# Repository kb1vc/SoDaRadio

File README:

SoDa -- A Software Defined Radio for the Ettus Research USRP

SoDaRadio is a multi-mode VHF/UHF/Microwave radio transciever
that runs on Linux.   It has been tested on several Ettus
USRP models including the N200/WBX, N210/WBX, N210/SBX, N200/UBX,
and the B210. 

For information on building, installing, and using SoDaRadio see
the github pages at https://kb1vc.github.io/SoDaRadio/

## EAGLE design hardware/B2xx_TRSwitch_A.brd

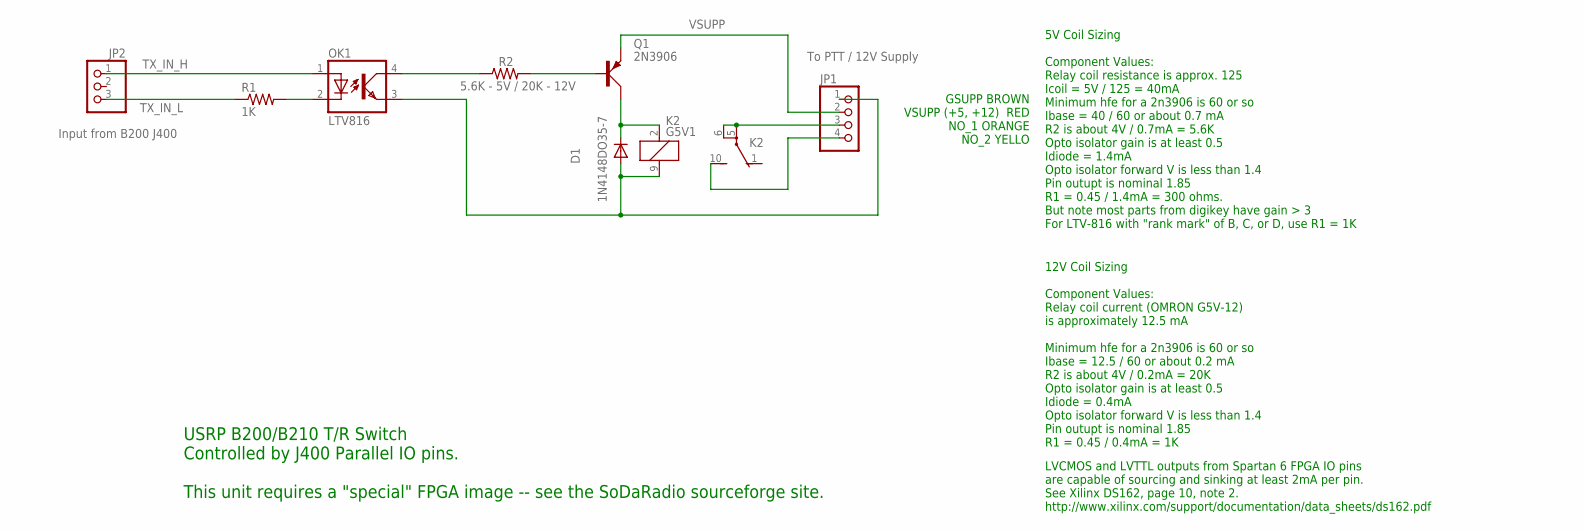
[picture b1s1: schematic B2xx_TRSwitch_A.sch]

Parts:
D1: 1N4148DO35-7; DO35-7
JP1: To PTT / 12V Supply; 1X04
JP2: Input from B200 J400; 1X03
K2: G5V1
OK1: LTV816; DIL04
Q1: 2N3906; TO92D
R1: 1K; AXIAL-0.3
R2: 5.6K - 5V / 20K - 12V; AXIAL-0.3

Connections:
GSUP_GND: D1.A, JP1.1, K2.9 (2), OK1.3 (EMIT)
unnamed: OK1.2 (C), R1.P$2 (2)
unnamed: OK1.4 (COL), R2.P$1 (1)
unnamed: Q1.B, R2.P$2 (2)
unnamed: D1.C, K2.2 (1), Q1.C
unnamed: JP1.3, K2.5, K2.6
unnamed: JP1.4, K2.10 (S)
TX_IN_H: JP2.1, OK1.1 (A)
TX_IN_L: JP2.3, R1.P$1 (1)
VSUPP: JP1.2, Q1.E

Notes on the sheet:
5V Coil Sizing Component Values: Relay coil resistance is approx. 125 Icoil = 5V / 125 = 40mA Minimum hfe for a 2n3906 is 60 or so Ibase = 40 / 60 or about 0.7 mA R2 is about 4V / 0.7mA = 5.6K Opto isolator gain is at least 0.5 Idiode = 1.4mA Opto isolator forward V is less than 1.4 Pin outupt is n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
12V Coil Sizing Component Values: Relay coil current (OMRON G5V-12) is approximately 12.5 mA Minimum hfe for a 2n3906 is 60 or so Ibase = 12.5 / 60 or about 0.2 mA R2 is about 4V / 0.2mA = 20K Opto isolator gain is at least 0.5 Idiode = 0.4mA Opto isolator forward V is less than 1.4 Pin outupt is n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
GSUPP BROWN VSUPP (+5, +12) RED NO_1 ORANGE NO_2 YELLO
LVCMOS and LVTTL outputs from Spartan 6 FPGA IO pins are capable of sourcing and sinking at least 2mA per pin. See Xilinx DS162, page 10, note 2. http://www.xilinx.com/support/documentation/data_sheets/ds162.pdf
USRP B200/B210 T/R Switch Controlled by J400 Parallel IO pins. This unit requires a "special" FPGA image -- see the SoDaRadio sourceforge site.

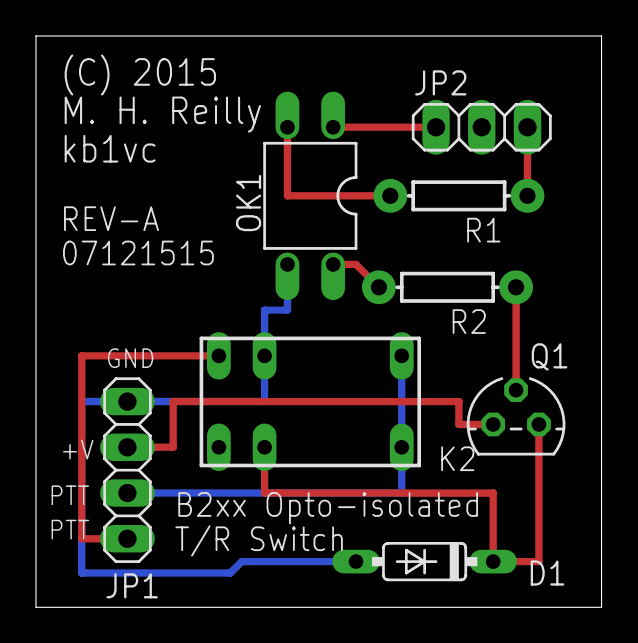
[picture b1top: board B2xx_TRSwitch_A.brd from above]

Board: 2 copper layers, 31.4 x 31.7 mm, 8 parts (0 on the bottom side), 10 nets.

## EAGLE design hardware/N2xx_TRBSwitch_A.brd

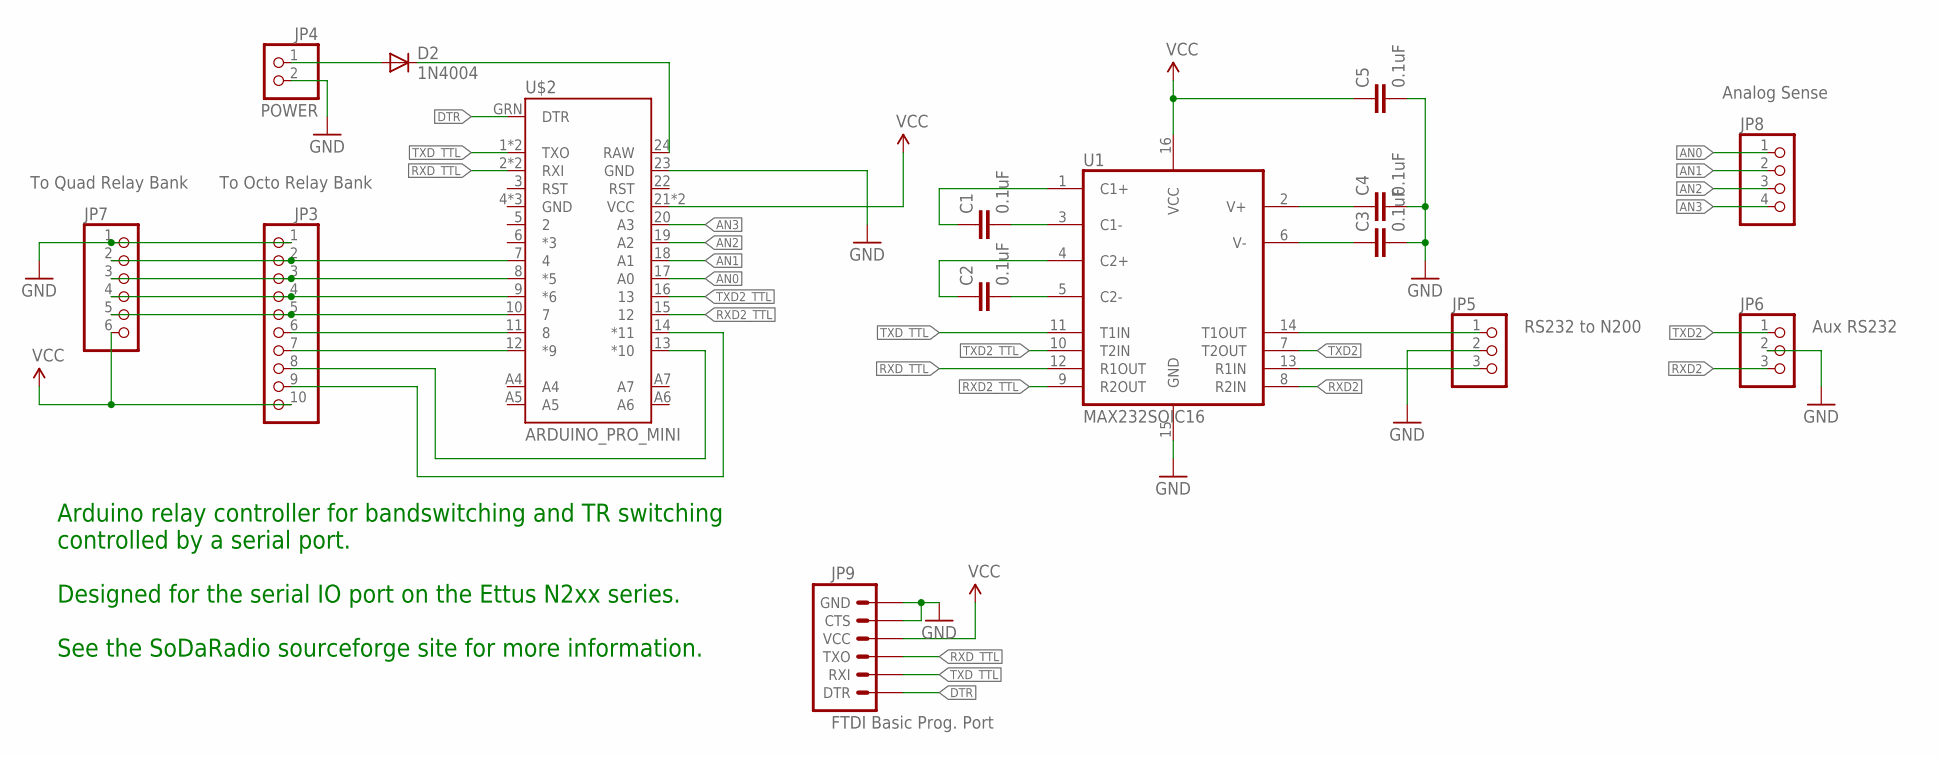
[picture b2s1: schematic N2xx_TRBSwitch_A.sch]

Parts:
C1, C2, C3, C4, C5: 0.1uF; 0805
D2: 1N4004; DO41-10
JP3: To Octo Relay Bank; 1X10
JP4: POWER; 1X02
JP5: RS232 to N200; 1X03
JP6: Aux RS232; 1X03
JP7: To Quad Relay Bank; 1X06
JP8: Analog Sense; 1X04
JP9: FTDI Basic Prog. Port; 1X06
U1: MAX232SOIC16; SO016
U$2: ARDUINO_PRO_MINI

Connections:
AN0: JP8.1, U$2.17 (A0)
AN1: JP8.2, U$2.18 (A1)
AN2: JP8.3, U$2.19 (A2)
AN3: JP8.4, U$2.20 (A3)
DTR: JP9.1 (DTR), U$2.GRN (DTR)
GND: C3.2, C4.2, C5.2, JP3.1, JP4.2, JP5.2, JP6.2, JP7.1, JP9.5 (CTS), JP9.6 (GND), U1.15 (GND), U$2.23 (GND)
unnamed: C1.2, U1.3 (C1-)
unnamed: C1.1, U1.1 (C1+)
unnamed: C2.1, U1.4 (C2+)
unnamed: C2.2, U1.5 (C2-)
unnamed: C3.1, U1.6 (V-)
unnamed: C4.1, U1.2 (V+)
unnamed: JP3.2, JP7.2, U$2.7 (4)
unnamed: JP3.3, JP7.3, U$2.8 (*5)
unnamed: JP3.4, JP7.4, U$2.9 (*6)
unnamed: JP3.5, JP7.5, U$2.10 (7)
unnamed: JP3.6, U$2.11 (8)
unnamed: JP3.7, U$2.12 (*9)
unnamed: D2.A, JP4.1
unnamed: JP5.1, U1.14 (T1OUT)
unnamed: JP3.8, U$2.13 (*10)
unnamed: JP3.9, U$2.14 (*11)
unnamed: JP5.3, U1.13 (R1IN)
unnamed: D2.C, U$2.24 (RAW)
RXD2: JP6.3, U1.8 (R2IN)
RXD2_TTL: U1.9 (R2OUT), U$2.15 (12)
RXD_TTL: JP9.3 (TXO), U1.12 (R1OUT), U$2.2 (RXI), U$2.RXI
TXD2: JP6.1, U1.7 (T2OUT)
TXD2_TTL: U1.10 (T2IN), U$2.16 (13)
TXD_TTL: JP9.2 (RXI), U1.11 (T1IN), U$2.1 (TXO), U$2.TXO
VCC: C5.1, JP3.10, JP7.6, JP9.4 (VCC), U1.16 (VCC), U$2.21 (VCC), U$2.VCC

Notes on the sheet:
Arduino relay controller for bandswitching and TR switching controlled by a serial port. Designed for the serial IO port on the Ettus N2xx series. See the SoDaRadio sourceforge site for more information.

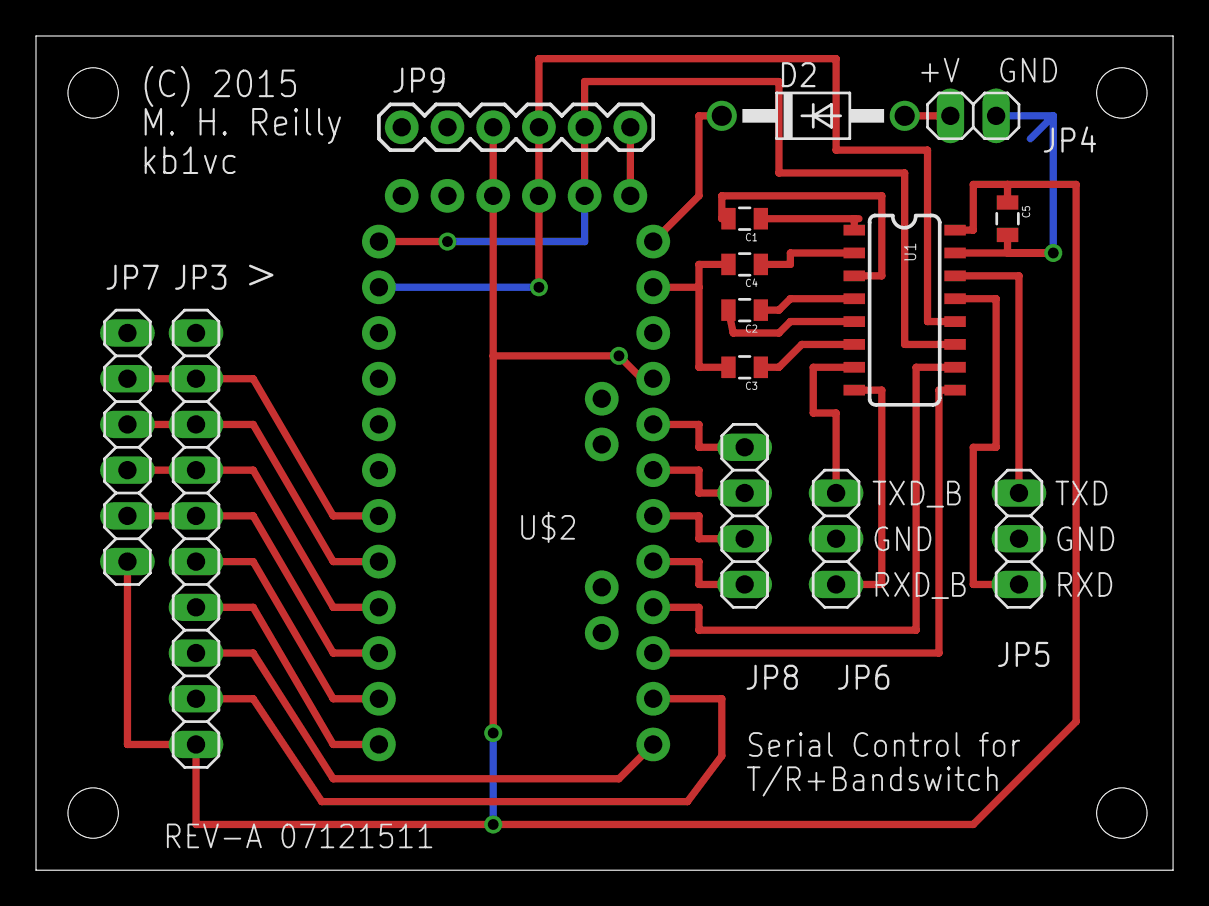
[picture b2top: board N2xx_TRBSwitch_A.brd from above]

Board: 2 copper layers, 63.2 x 46.3 mm, 15 parts (0 on the bottom side), 31 nets.

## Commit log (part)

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2017-09-16 Fixed build problem wrt gpslib.
2017-09-16 moved doxygen to docs subdir -- will that help?
2017-09-16 Removed dead Demod.[ch]xx and TSIP files.
2017-09-24 The log handler was writing empty log files. That's a bit of an annoyance, so the closing code now checks to see if the log file is 0 length. If the current output log file is empty, it will be delet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
    If a new log file is opened, then the old file is closed. A zero
    length file will be deleted.
    While testing, I found a memory leak that was triggered by calls
    to libgps. After much experimentation, and the addition of a
    switch to the soda server command:
    SoDaRadio --serverargs "--report_file soda_mem_use.dat"
2017-09-26 Added Fedora 26 rpm for version 5.0.3.
    Updated README.md to point to new kit.
2017-10-07 working on lime port
2017-10-21 Fixed a few problems with RX and TX freq change reporting to hamlib server
2018-03-24 Added Ubuntu-17.10 package
2018-03-24 Removed debug print from hamlib_listener
2018-03-24 Added new 5.1.5 package for Ubuntu 16.04
2018-03-28 Fixed startup instructions in README.md as per a note from hb9dug -- merci michel...
2018-04-17 Removed frequent and repeated debug messages from AudioALSA left over from the great ALSA race chase of a few weeks ago.
    Now the --debug switch can be useful again.
2018-08-23 Added buffer pool manager BufferPool.hxx
    AudioIfc now only supports float datatypes
    BaseBandRX improved handling of buffer under-runs in the outbound audio.
    Switched to AudioPA for the audio interface. This is temporary, and
    was done to verify that the audio dropout problems were caused by running
    out of waiting buffers.
2018-08-26 Added FindPortAudio.cmake to cmake modules.
2018-08-29 More work on rate matching radio stream to audio output. The previous attempt saw the audio fall behind by several seconds over the course of a day. It is clear that activity on the host computer can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
    The new scheme limits the run-ahead and also stuffs zeros until we have
    at least 5 frames worth of audio available in the circular buffer.
    I suspect we'll need to implement sample cutting to allow the audio
    to catch up, but sample cutting doesn't help if the fall-behind events
    get one second behind.
    This may be a linux real-time issue.
2018-08-31 updated the README.md file.
2018-09-01 Added Ubuntu 18.04 package.
    Updated README.md file to indicate no more kits for 16.04 since Ubuntu
    did not update Qt5 support after the first release of 16.04.
2018-09-01 Updated README.md for new Ubuntu kit
2018-09-02 qtgui:
    Added labels to Sidetone and TX power to show current levels.
2018-09-07 Switched audio recording to FLAC -- lossless and more compressed than WAV uLaw...
    merged back tool tips that got lost earlier.
    Added tool tip for RECORD checkbox.
    Added FindSndFile.cmake to find libsndfile stuff.
    Added libsndfile requirements to deb and rpm package instructions.
    Tested on fedora. Ubuntu needs to be tested.
2018-09-07 Fixed file problem in record audio -- file name was badly formed.
2018-12-05 Modified GUI layout to put most-used buttons in a cluster. Previous arrangements were awkward, requiring a mouse excursion from one side of the screen to the other just to TX/RX/log a contact. Perhap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
2019-01-12 Tuning audio buffer sizes (in the gui) to make sure we don't have drop-outs (because the radio server/demod/socket-link have fallen behind) or excessive delays (because Qt Audio got behind)... Up unt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
2019-01-15 Added notes to explain changes to transmit tuning.
2019-01-20 NBFM has a squelch setting on the SETTINGS tab. It is unitless, and its setting is relative to the RF gain setting, so the two interact... sigh. The alternative would scan the whole IF span and look 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
    In operation, once a particular squelch level is set, the RF gain can be
    adjusted up/down to get a little more control over the breakpoint.
    The squelch setting is stuck on the Settings page because there isn't
    sufficient room on the main panel for a control that is only used in NBFM
    mode.
    Hang time for the squelch is
2019-01-21 Removed obsolete packages.
    Added deb package for V6.4.1 on Ubuntu 18.04
    Added rpm package for V6.4.1 on Fedora 28
    Added UHD rpm package for UHD V3.14.0 on Fedora 28
2019-01-21 Ubuntu is not working in a VM... is it broken on real systems?
2019-01-22 Debian packages for Ubuntu were missing libqt5multimedia5-plugins. The radio would run, but it would find no audio devices. The new package instructions cause this package to get loaded when SoDaRadi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
2019-03-10 First steps in providing a "Satellite" mode -- TX and RX frequencies are separated by a fixed amount, set in the Config Band tab. This mode is primarily for the QO-100 geosync satellite.
    To enable this mode,
    1. Create a new band setting in the "Config Band" panel.
    2. Check the "Enable TX/RX Offset" box.
    3. Enter the offset to be added to the RX frequency that will produce
    the TX frequency. Enter this in MHz.
    Now when TX=RX Lock is set, the two frequencies will track with the
2019-04-23 Changed gain scheme for WBFM and NBFM in BaseBandRX. The audio gain was far too low in WBFM mode, and rather hit-and-miss for NBFM.
    In the absence of AVC or AGC, this is all hit-and-miss. But at
    least now the FM audio level is similar to the USB/CW/AM audio
    levels for reasonably strong signals.
2019-12-15 Reorganize thread objects so that they register themselves and select which mailboxes they subscribe to. This removes the control from SoDaServer.
    All this is in preparation for "loadable modules" that can
    attach to any of the mailboxes. (Think loadable modems...)
    There were several objects who's class name was something like
    SoDa::SoDaFoo. These have now been changed to SoDa::Foo
2019-12-30 There were problems with SoDaRadio on Fedora 30 -- the audio listener code in the GUI enumerated many audio devices, some of which could not support the 48kS/s sample rate. (SURROUND20, for instance)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
    The changes here addressed this issue:
    1. At enumeration time, only those audio devices that support the sample
    rate and format requirements will be listed in the combobox audio output
    device menu.
    2. If the stored selection from the settings file is invalid, the first
    item in the audio output device list (the default device) w
2019-12-31 Added CMake support for the example directory... This includes SoDaRadioConfig[Version].cmake to be installed in lib/cmake/...
    Next step is to add some doxygen docs for loadable modules.
2020-01-01 actually committed files missed by previous commit 5ea4f04.
2020-04-12 Code clean up (just the beginning). Also added config directory/file for VSCode.
    1. Deboostify components in qtgui, as most boost components
    have either been supplanted by C++11 features (e.g. BOOST_FOREACH)
    or are better done with Qt native stuff (e.g. boost::format).
    a) Remove all references to boost::format in qtgui/*
    b) Remove all uses of BOOST_FOREACH in qtgui/*
    2. Clean up replicated code in soda_listener.cpp -- in all the
2020-05-02 B200mini TX-RX via GPIO
    USRPCtrl.cxx: file was not touched
2020-11-27 Fixed another issue with #11 -- GPSmon was still being built with calls to gpslib even when libgps was disabled with DISABLE_GPSD
    src/CMakeLists.txt
    Fixed setup of gpsd -- disabled if DISABLE_GPSD was set.
    CMakeLists.txt
    Bumped patch number.
2020-12-01 Bumped version patch number after gps fixes
2020-12-06 Beginning transition of TX from ALSA
2020-12-06 Fixing Qt package search for MacOS
2020-12-09 Builds under MacOS Catalina! Requires QWT fixes -- see MacOS_Hints.txt
2020-12-31 First commit -- appears to work.
2021-01-01 Fixed cmake stuff.
2021-01-01 Added BSD2 license to Format.[ch]xx
2021-02-07 Working on submodules and such.
2021-02-08 working on qwt
2021-04-28 mode_n=integer formatting is broken in USRPCtrl.cxx -- likely SoDaFormat
2022-02-19 One more block o stuff removed.
2022-02-20 conversion to sodasignals has to wait for re-architected mailbox scheme.
2022-06-20 Fixed name collision with new SoDa Utils SoDa::Exception class.
    Ooops.
    matt
2022-07-04 Something is wrong with the spectrum display
2022-07-05 Seems to work now.
2022-07-10 Progress. USRP is now a generic module and the server starts a radio based on a radio type "USRP" with HackRF, Pluto and RTLSDR to follow.
    Next step is to re-do the resamplers, as RTLSDR and others don't want to
    use the same sample rate as the USRP.
2022-07-23 Fixes to enable build on Ubuntu 20.04 LTS.
    This included fixes to handling lib vs lib64 problems in the "foreign"
    SoDaUtils include.
    There is a "fix" in soda_hamlib_handler.cpp that reverts to an
    about-to-be-deprecated argument to QString split. This should get
    fixed with something that doesn't trigger a warning on more
    contemporary Qt installations.
2022-07-30 Rework Resampler, Filter, and OSFilter scheme.
2022-08-14 Jupyter model of resampler looks good.
2022-10-01 Massive rework in progress.
    It compiles, doubt that it runs yet.
    1. Eliminated old OSfilter, renamers and other stuff that is now in
    the separate SoDa::Signals library.
    2. Eliminated the hilbert transformer uses in SSB and others. Performance
    around DC is just too janky.
    3. Made sample rates and buffer sizes parameters. The latter are originated
2022-11-11 Removed SoDaRadio_Band.hxx
    Cleaned up references to CircularBuffer.hxx after deleting and then
    restoring it.
2022-12-31 server args get passed, but not well
2023-04-23 trying to find leak
2023-05-07 Fixes for new version of qt and qwt
2023-05-27 starting to figure out the plotting problem. setAxis ?
2023-10-21 Still trying to find the issue.
2024-11-17 Fixing transmit with new QT configuration
2024-12-07 Changed stream pointers to smart pointers
2025-06-19 temporary
2025-06-22 removed boost dependency from cmake
2025-06-22 No sound. No graphics. No joy.
2025-11-11 rx appears to work.
2025-11-15 Progress.
    1. Need to fix transverter offset code (for Ham-it-up high side injection)
    2. Update to QT6.
    3. Add audio path from qtgui to radio - eliminate dependence on problematic
    auto libraries and such. (And offer a better way to connect the audio TX chain.)
    The qt6 update will happen first, because I anticipate problems with item
    3. The qt5 documentation and support appears to be withering away. Despite
2025-11-16 A little cleaner. perhaps.
2025-12-28 minor changes to fix refs to sodalibs and boost
2026-01-19 1. Changed BaseBandRX to apply audio filter *after* SSB demod. The filter was ill-shaped for LSB (it was single sided) so LSB demod was really bad.
    2. AudioQt was segfaulting due to a missing call to mbx subscribe.
    3. Added some thread debugging hooks that do no good at all.
2026-01-26 Holy cow! This compiles under Qt6. The key hurdle was in fiding out that QAudioOutput and QAudioInput were replaced by QAudioSink and QAudioSource. This was from a Qt video thingie: https://www.qt.io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
    Still don't know if it works... but here goes.
2026-05-21 About to fix problem with namespace collision...sigh.
2026-06-13 RX is working in TestCLI - at least it hears a single tone at about the right frequency.
    TX is working in TestCLI - it sends a single (beacon) tone at about the
    right frequency.

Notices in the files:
hardware/B2xx_TRSwitch_A.brd:
(C) 2015
hardware/B2xx_TRSwitch_A.sch:
(C) 2015 Matt Reilly -- kb1vc
parts and their libraries:
SparkFun-Passives: Licensing: Creative Commons ShareAlike 4.0 International - https://creativecommons.org/licenses/by-sa/4.0
